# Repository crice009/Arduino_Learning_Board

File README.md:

# Arduino_Learning_Board
A set of resources to help with teaching and learning the skills of Arduino: coding, soldering, electronics, inputs and outputs. These include Arduino shield designs, BOM for ordering supplies, example sketches and a simple website for guiding structured learning/ play with these resources.

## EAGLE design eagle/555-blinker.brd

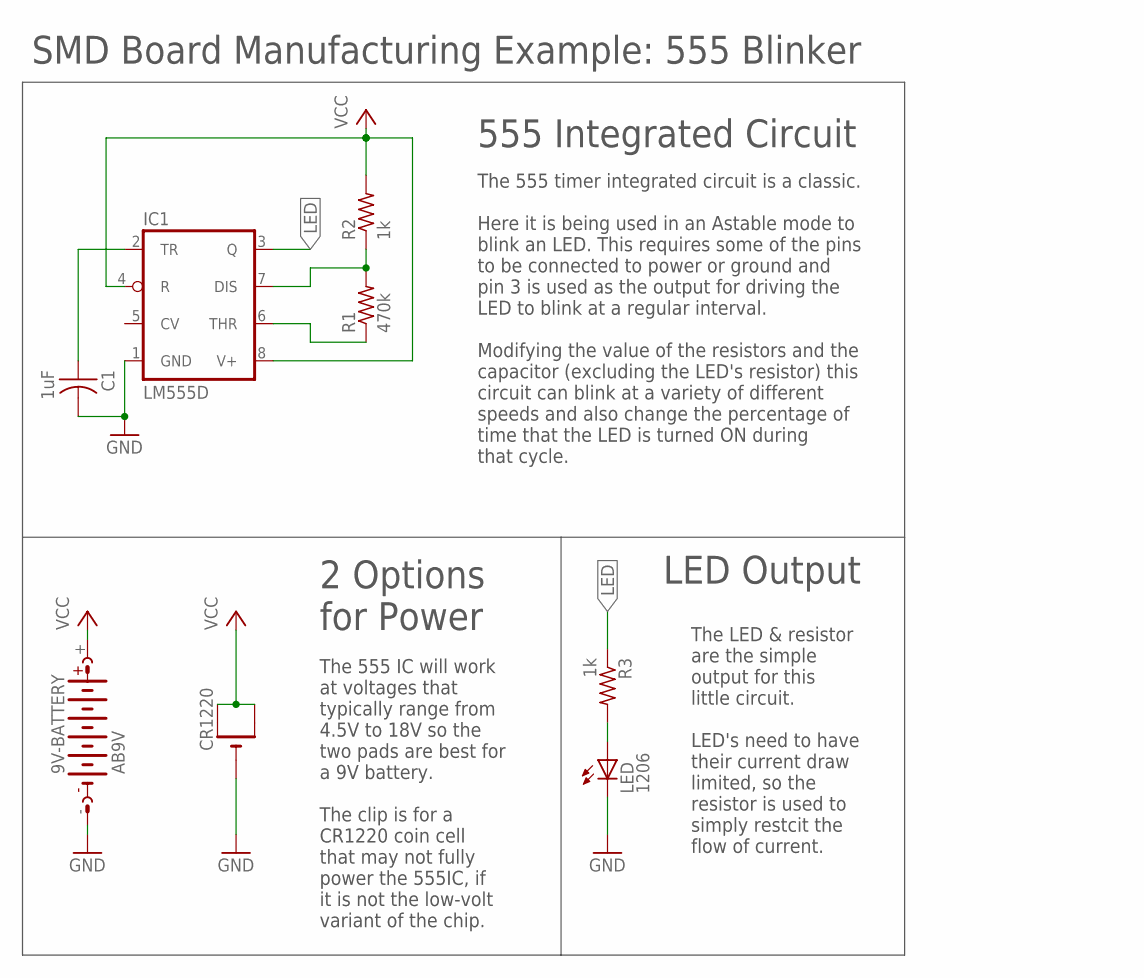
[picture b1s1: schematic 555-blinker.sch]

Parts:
9V-BATTERY: AB9V
C1: 1uF; C1206FAB
CR1220: CR1220SMT; CR1220-SMD
IC1: LM555D; SO08
LED: 1206; LED1206FAB
R1: 470k; R1206FAB
R2, R3: 1k; R1206FAB

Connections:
GND: 9V-BATTERY.-, C1.2, CR1220.-, IC1.1 (GND), LED.2 (C)
LED: IC1.3 (Q), R3.1
unnamed: IC1.7 (DIS), R1.2, R2.1
unnamed: IC1.6 (THR), R1.1
unnamed: C1.1, IC1.2 (TR)
unnamed: LED.1 (A), R3.2
VCC: 9V-BATTERY.+, CR1220.+$1 (+), CR1220.+$2 (+1), IC1.4 (R), IC1.8 (V+), R2.2

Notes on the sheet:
SMD Board Manufacturing Example: 555 Blinker
555 Integrated Circuit
2 Options for Power
LED Output
The 555 timer integrated circuit is a classic. Here it is being used in an Astable mode to blink an LED. This requires some of the pins to be connected to power or ground and pin 3 is used as the output for driving the LED to blink at a regular interval. Modifying the value of the resistors and the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
The 555 IC will work at voltages that typically range from 4.5V to 18V so the two pads are best for a 9V battery. The clip is for a CR1220 coin cell that may not fully power the 555IC, if it is not the low-volt variant of the chip.
The LED & resistor are the simple output for this little circuit. LED's need to have their current draw limited, so the resistor is used to simply restcit the flow of current.

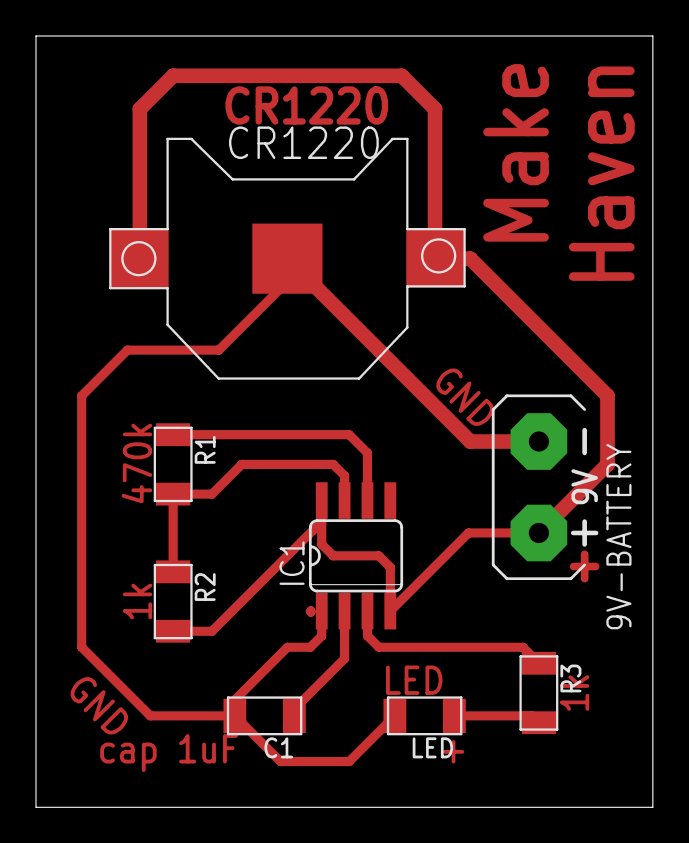
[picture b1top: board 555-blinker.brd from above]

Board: 2 copper layers, 34.3 x 42.9 mm, 8 parts (0 on the bottom side), 7 nets.

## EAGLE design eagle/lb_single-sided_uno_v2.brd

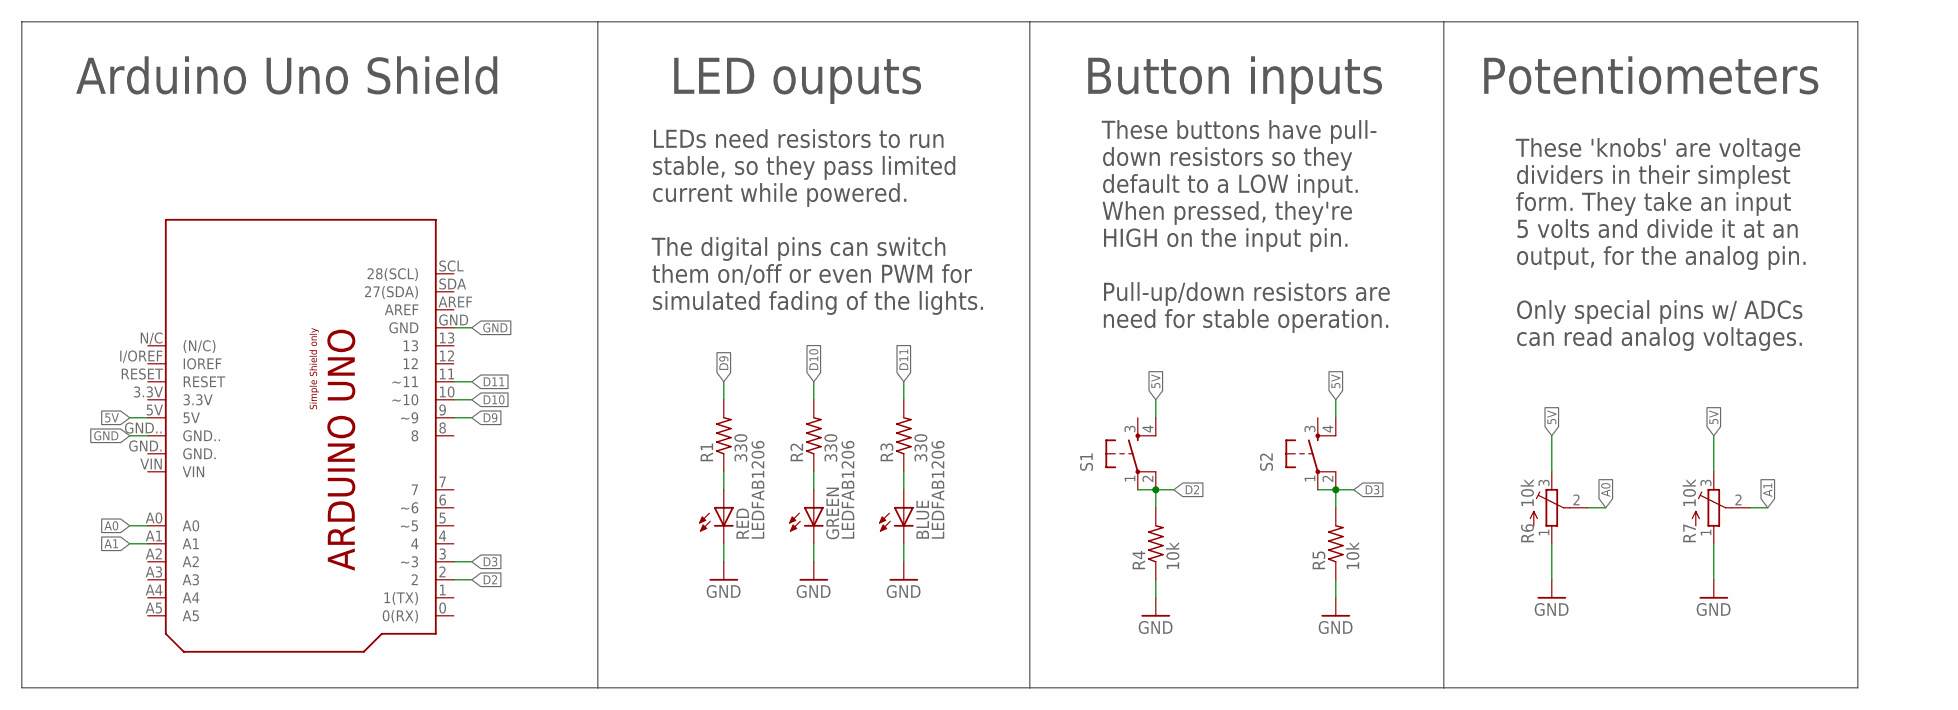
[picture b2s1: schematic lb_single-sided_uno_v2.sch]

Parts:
BLUE: LEDFAB1206; LED1206FAB
GREEN: LEDFAB1206; LED1206FAB
PCB1: ARDUINO_UNO_V2
R1, R2, R3: 330; R1206FAB
R4, R5: 10k; R1206FAB
R6, R7: 10k; TC33X
RED: LEDFAB1206; LED1206FAB
S1, S2: 6MM_SWITCH6MM_SWITCH; 6MM_SWITCH

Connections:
5V: PCB1.5V, R6.3 (E), R7.3 (E), S1.4 (S1), S2.4 (S1)
A0: PCB1.A0, R6.2 (S)
A1: PCB1.A1, R7.2 (S)
D2: PCB1.2, R4.2, S1.1, S1.2 (P1)
D3: PCB1.3 (~3), R5.2, S2.1, S2.2 (P1)
D9: PCB1.9 (~9), R1.2
D10: PCB1.10 (~10), R2.2
D11: PCB1.11 (~11), R3.2
GND: BLUE.2 (C), GREEN.2 (C), PCB1.GND, PCB1.GND.., R4.1, R5.1, R6.1 (A), R7.1 (A), RED.2 (C)
unnamed: R1.1, RED.1 (A)
unnamed: GREEN.1 (A), R2.1
unnamed: BLUE.1 (A), R3.1

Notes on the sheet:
Arduino Uno Shield
LED ouputs
Button inputs
LEDs need resistors to run stable, so they pass limited current while powered. The digital pins can switch them on/off or even PWM for simulated fading of the lights.
These buttons have pull- down resistors so they default to a LOW input. When pressed, they're HIGH on the input pin. Pull-up/down resistors are need for stable operation.
Potentiometers
These 'knobs' are voltage dividers in their simplest form. They take an input 5 volts and divide it at an output, for the analog pin. Only special pins w/ ADCs can read analog voltages.

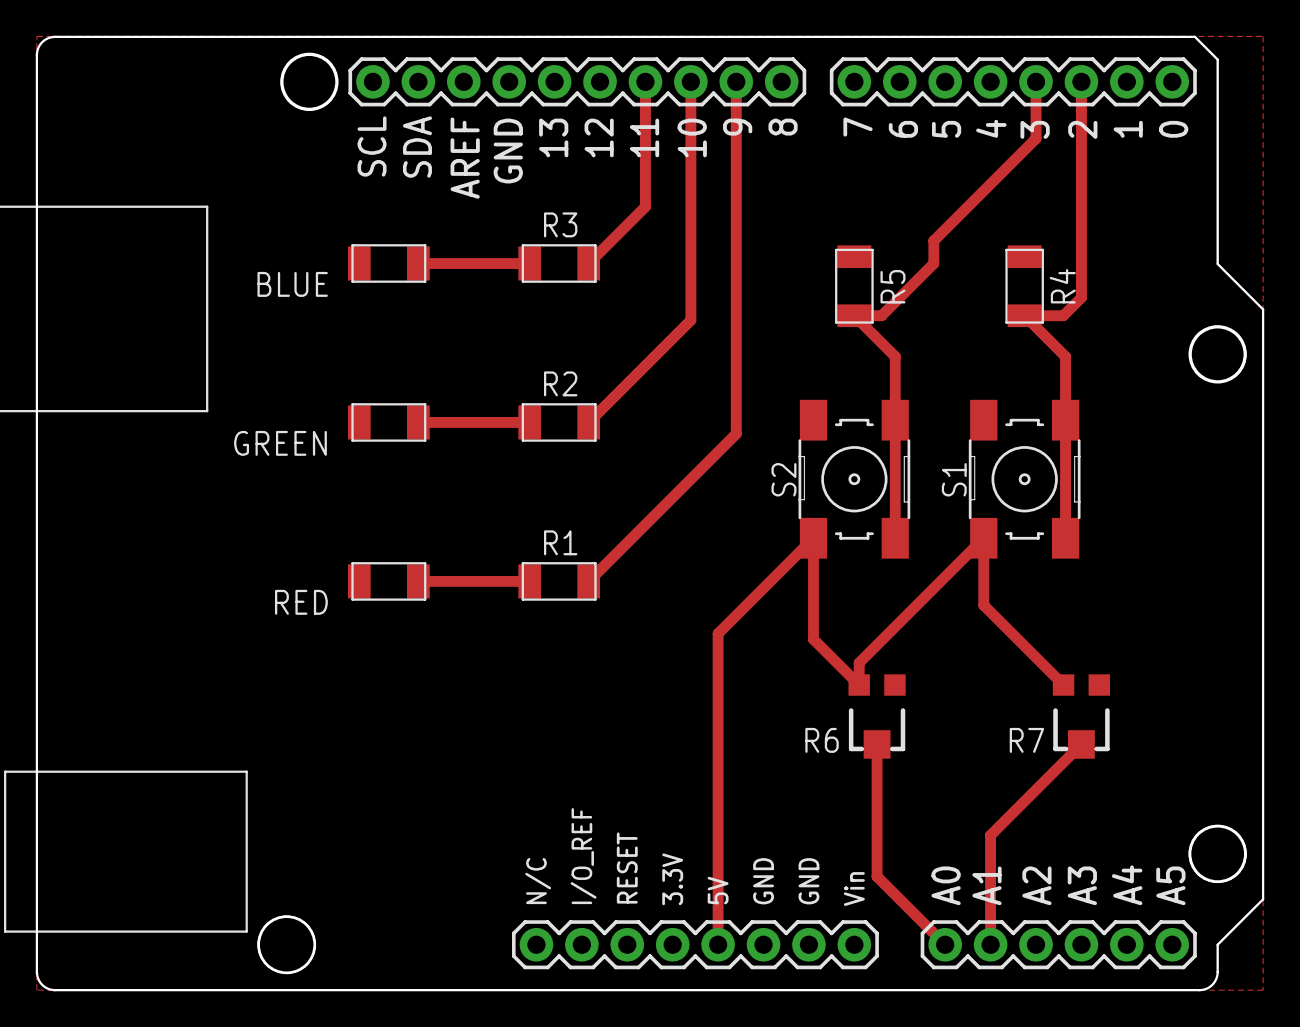
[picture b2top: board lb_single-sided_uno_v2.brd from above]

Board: 2 copper layers, 68.6 x 53.3 mm, 13 parts (0 on the bottom side), 12 nets.

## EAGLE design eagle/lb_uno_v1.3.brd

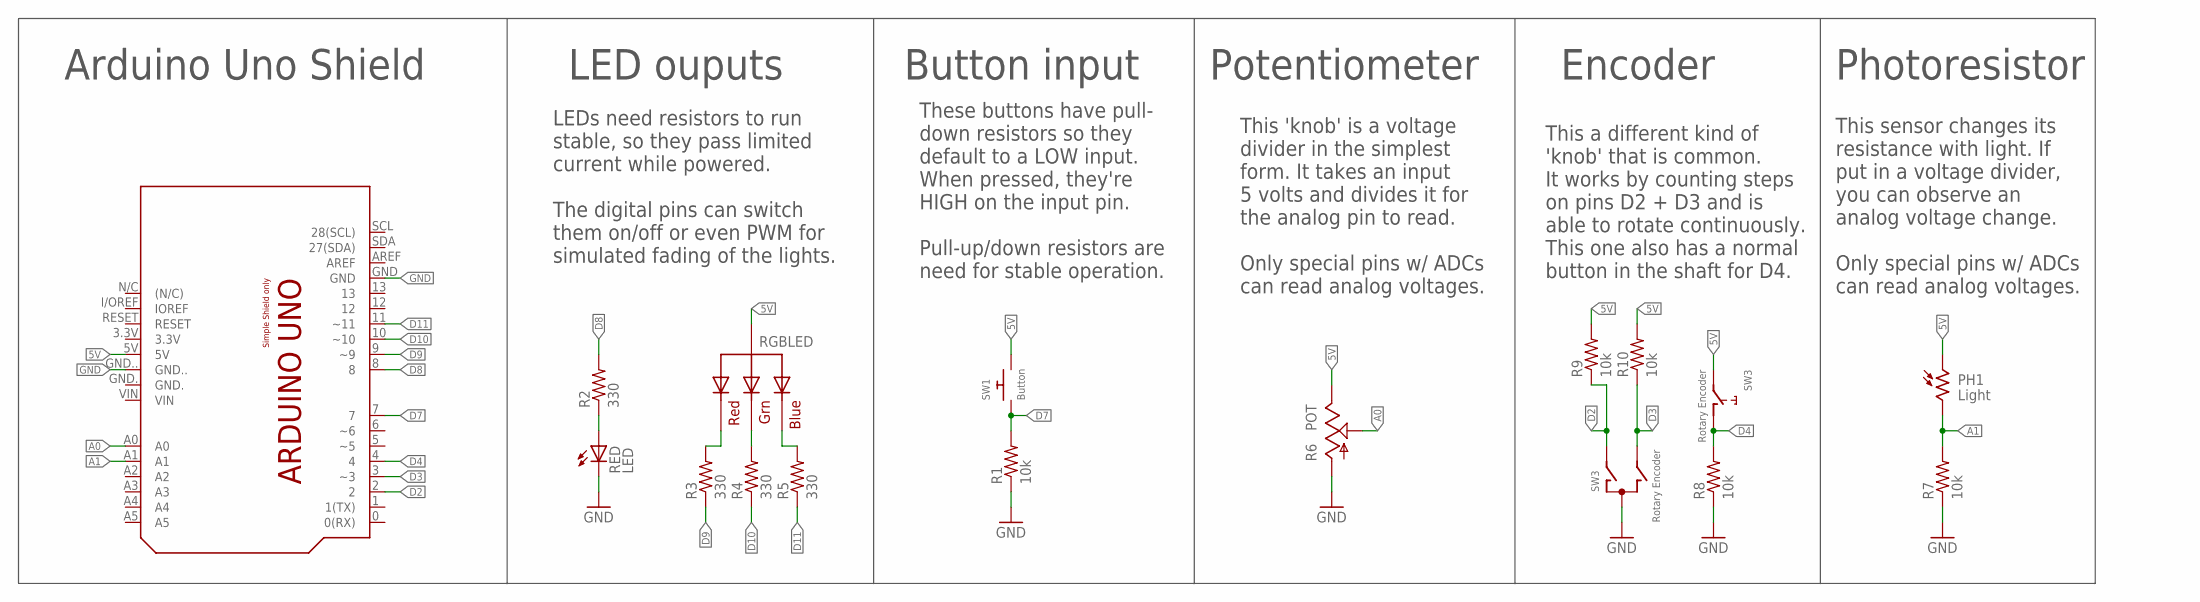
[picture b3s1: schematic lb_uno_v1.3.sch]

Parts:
PCB1: ARDUINO_UNO_V2
PH1: Light; T0-46-A10XX
R1, R7, R8, R9, R10: 10k; 0207/9
R2, R3, R4, R5: 330; 0207/9
R6: POT; B25P
RED: LED; 5MM
RGBLED: RGBLED; LED5MMRGB
SW1: Button; TACT_PANA-EVQ
SW3: Rotary Encoder; ALPS_EC12E_SW

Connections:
5V: PCB1.5V, PH1.1, R6.E, R9.2, R10.2, RGBLED.2 (VCC), SW1.P$2, SW3.E (2)
A0: PCB1.A0, R6.S
A1: PCB1.A1, PH1.2, R7.2
D2: PCB1.2, R9.1, SW3.A
D3: PCB1.3 (~3), R10.1, SW3.B
D4: PCB1.4, R8.2, SW3.D (1)
D7: PCB1.7, R1.2, SW1.P$1
D8: PCB1.8, R2.2
D9: PCB1.9 (~9), R3.1
D10: PCB1.10 (~10), R4.1
D11: PCB1.11 (~11), R5.1
GND: PCB1.GND, PCB1.GND.., R1.1, R6.A, R7.1, R8.1, RED.OUT (C), SW3.C
unnamed: R2.1, RED.IN (A)
unnamed: R3.2, RGBLED.1 (RED)
unnamed: R4.2, RGBLED.3 (GREEN)
unnamed: R5.2, RGBLED.4 (BLUE)

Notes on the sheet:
Arduino Uno Shield
LED ouputs
Button input
LEDs need resistors to run stable, so they pass limited current while powered. The digital pins can switch them on/off or even PWM for simulated fading of the lights.
These buttons have pull- down resistors so they default to a LOW input. When pressed, they're HIGH on the input pin. Pull-up/down resistors are need for stable operation.
Potentiometer
This 'knob' is a voltage divider in the simplest form. It takes an input 5 volts and divides it for the analog pin to read. Only special pins w/ ADCs can read analog voltages.
Encoder
This a different kind of 'knob' that is common. It works by counting steps on pins D2 + D3 and is able to rotate continuously. This one also has a normal button in the shaft for D4.
Photoresistor
This sensor changes its resistance with light. If put in a voltage divider, you can observe an analog voltage change. Only special pins w/ ADCs can read analog voltages.

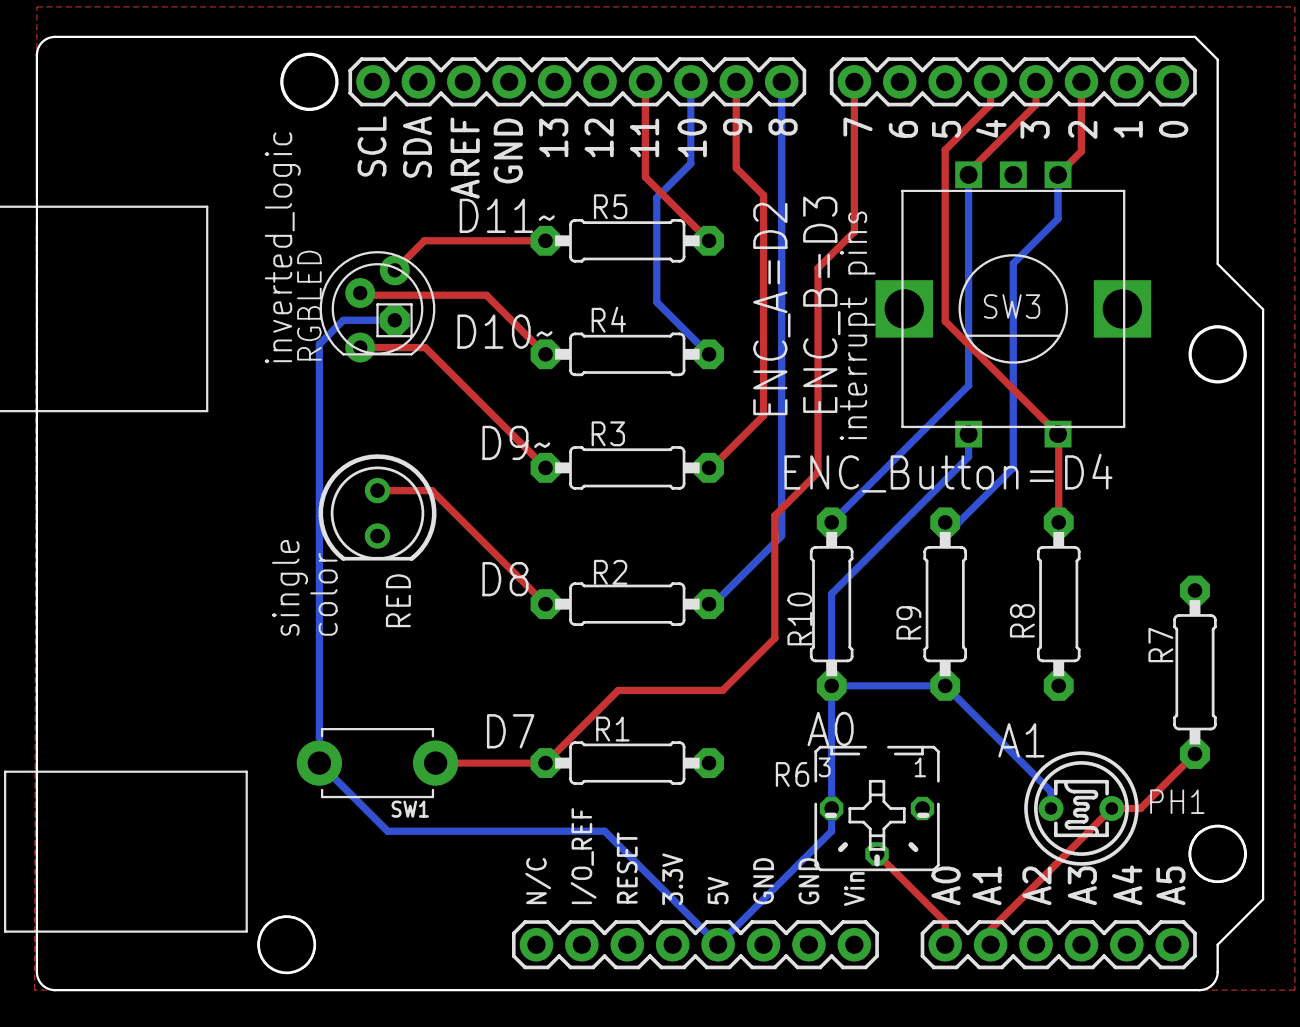
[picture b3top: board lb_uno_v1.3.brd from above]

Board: 2 copper layers, 68.6 x 53.3 mm, 16 parts (0 on the bottom side), 16 nets.

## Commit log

2020-07-18 first reaal commit
2020-07-18 fixed the image in readme.md
2020-07-19 needed to change the single sided board to SMD parts so they are solderable & provide practice
2020-07-20 updated board designs and docs
2020-07-20 links added in docs
2020-07-20 stylesheet added to Docs and links kind-of fixed?...silly GitHub
2020-07-20 last commit didnt catch stylesheet
2020-07-20 byline added
2020-07-20 silly GitHub pages...
2020-07-20 added bill of materials
2020-07-20 formatted bill of materials for preentation on the web
2020-07-20 font change
2020-07-20 more css set-up
2020-07-20 added arduino sketch examples
2020-07-20 added notes after Nick looked at the docs page
2020-07-20 updated commentary in arduino sketches
2020-07-20 added placeholder for nick to see
2020-07-20 responsive break sizes changed
2020-10-10 added 555 circuit
2020-10-11 github is strange about adding relative links when you use a docs folder for a website...
2020-10-11 2x github is strange about adding relative links when you use a docs folder for a website...
2020-10-11 3x github is strange about adding relative links when you use a docs folder for a website...
2020-10-11 added BOM for 555 circuit
2020-10-11 4x github is strange about adding relative links when you use a docs folder for a website...
2020-10-11 added viewport line to html
2020-10-11 updated gerber files link
